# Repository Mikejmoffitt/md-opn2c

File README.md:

# MD用YM3438アダプター・MD YM3438 Adapter

# 概要・Overview
このアダプターでメガドライブ初代はYM3438(OPN2C)が対応できるようになります。　元々の音源のステータスレジスターの読み込みの違いを解決するとジックがついています。　その上[オープンソースのトリップルバイパス](https://github.com/tianfeng33/triple-bypass-Version-2))より綺麗な音源のミクサーとバッファーがついていて、元々のヘッドホンも専用ライン出力が使えるようになります。

元々のFM音源(YM2612)を抜いて使用することも可能です。　その場合は[3BP](https://github.com/tianfeng33/triple-bypass-Version-2)と同じような使い方になります。　その場合でもヘッドホンもラインアウトも利用できます。

メガドラVA0の基板を参考しながら書いたんですが、基本的にすべての初代の基板は互換はずです。

This adapter facilitates the install of a YM3438 (OPN2C) in a Sega Mega Drive or Genesis console. Glue logic is present to solve status read bugs that invoke different behavior between the original YM2612 and the CMOS YM3438. In addition, a mixing and buffering circuit (courtesy of [the open source Triple Bypass PCB](https://github.com/tianfeng33/triple-bypass-Version-2)) to both handle the new YM3438 and also provide clean mixing for other signals. The buffer circuit also has provisions to output audio to the original signal path, so that the mono audio output and the headphone jack both work as designed.

An original YM2612 may also be installed, in which case this PCB simply provides a new mixing circuit and buffer, similar to the [Triple Bypass PCB](https://github.com/tianfeng33/triple-bypass-Version-2)).

These instructions were written using a Japanese VA0 unit as a reference, but principally can apply to any Megadrive or Genesis with a YM2612 in it.

## 互換の本体・Compatibility

メガドライブ（初代）VA0-VA6は互換です。 ジェネシス２のVA3でも動くかもしれませんが、未確認なので一応保証ができません。
Compatible with Genesis 1 / Megadrive 1 VA0-VA6. Genesis 2 VA3 (with discrete YM2612) may work, but has not been tested, and I cannot provide installation instructions at this time.

# 設置・Installation

## マザーの修正・Motherboard Preparation

マザーに付ける前に修正が必要です．

With the adapter unit ready, some work must be done to the Megadrive motherboard.

YM2612を外して、どこか保存しします。（依頼要らないけど捨てないでください！）　下の縦列のコンデンサーも外しましょう。(C40, C41, C42, C43, C44, C61, C62)

Desolder and remove the YM2612, and the column of capacitors below it (C40, C41, C42, C43, C44, C61, and C62).

底面に赤く示している部品を外します。 (R34, R37, R40, R41, C45, C46, C47, C48)。　右の黄色いやつを外して、左のバツが付いている黄色い部品をその位置に移動します (R53/R43, R40/R41)。　C41とC43の穴にリンクを入れてください。

下面に印刷がないので下の絵を参考してください。

On the underside, remove the components marked in red (R34, R37, R40, R41, C45, C46, C47, C48). Remove the components marked in yellow (R53 and R43) and move them to the spot marked in yellow (R40 and R41). Install a link between the two pins of capacitors C41 and C43.

As there is no silkscreen on the underside of most revisions, the diagram will be a helpful reference. 

新しいミックスされた音声は元々のFM音源の端子に入ります（21ピンと20ピン）。　そのために元々のヘッドホンもモノの出力が使えます。

The new audio will enter through what used to be the MOL and MOR pins for the OPN2, at pins 21 and 20 respectively. The mixed stereo signals enter the original mixing circuit alone, where it then enters the headphone amp as well as the mono mixdown for the CXA-1145.

## 音源付け方・Installation of FM Sound Source

YM3438か先抜いたYM2612をアダプターの上面に付けます。　下面にピンが邪魔になってしまうので上面にハンダ付けても大丈夫です。　音源のICは完全に平にならないんですが、全ての端子がちゃんとついていたら問題がありません　(少距離は大丈夫です)。

アダプターのウラ面にジャンパーがあります。　音源の種類によって左側か右側を半田で閉めて下さい。　両方のジャンパーを同じ設置するようにご注意下さい。

Attach either a YM3438 or the previously removed YM2612 in the open position on the adapter PCB. As the header pins on the underside may obstruct your soldering, it is fine to apply solder on the top side. The IC may not lay perfectly flat, but if all pins are firmly soldered a slight distance is acceptable.

On the underside of the adapter, use solder to close the jumpers based on the sound source type. You must set both sets of jumpers in the same configuration.

| 設定Config | IC類Chip |
|------------|----------|
| `(---  )`  | YM2612   |
| `(  ---)`  | YM3438   |

YM2612の場合は、音源の20/21ピンからグラウンド(19ピン）に2.2k抵抗器を付けて下さい。　次の改正に修正しますが、とりあえずこの小さい改造が必要になります。

In the case of a YM2612, attach two 2.2k resistors between pins 20/21 and ground (pin 19), as the YM2612 requires pulldown resistors. Pads for this will be incorporated in a future revision.

## 基板の付け方・Installation in Megadrive

先の準備を完全似できたか確認しておいてください。

Please be sure you have completed the Motherboard Preparation steps first.

YM2612の位置にYM3438のアダプターを入れて、下面にハンダ付けます。　上面に5本の配線が必要です。　下の表を参考して

Place the assembled YM3438 adapter unit in the position that once held the original YM2612, and solder it in place on the underside. On the top, five wires are necessary to feed in the various audio signals that compliment the FM sound source. The table below describes the positions shown in the annotated picture below.

| 信号Signal | 出所Location |
|------------|--------------|
| SL1        | C42 (-)      |
| SL2        | C61 (-)      |
| SR1        | C44 (-)      |
| PSG        | C40 (-)      |
| SR2        | C62 (-)      |

これで、どうやって出力を本体外に出すか自分の決まりです。　もしヘッドホンの端子が十分でしたらここまでストップしても大丈夫です。　しかし、ヘッドホンのアンプより直接LINE出力したらノイズが少なくなるので、LINEの出力はおすすめです。

アダプターにOUTのパッドがあります。　そこに配線付けて端子に繋げたらLINEの出力が可能です。

With everything installed, it's up to you how you want to route the audio out. If the headphone jack alone is adequate, you may stop here. However, I recommend a dedicated line out connection, as the headphone amp does introduce some noise.

The 'LINE OUT' pads are present so you may run a stereo output to the back of the console, or to some other connector of your choosing. Stereo audio will be present via the headphone jack, and mono audio will be delivered out of the rear A/V connector.

# フィルター調整・Filter Adjustment

アダプタのLPFフィルターの遮断周波数は約16KHzになっていますが、もしVA3みたいな~3KHzは希望だったらコンデンサー交換通じて可能です。　示しているコンデンサーを150Pfに交換すると、LPFの遮断周波数は~3KHzになります。　元々のは33pFです。

The filter situated on the adapter has a fairly high cutoff frequency of about 16KHz. Unlike the triple bypass PCB, there isn't a selection of filter parameters, but if a stronger filter that sounds similar to the VA3 is desired, you may exchange the two highlighted capacitors for 150pF units to achieve a ~3.5KHz cutoff. The originals are 33pF.

# バージョン・Version History

## 1.0.0

テスト用基板です。　YM2612対応パッドがなくてYM3438だけを確認しました。

This version was made for testing. Pads to cooperate with YM2612 were not considered, and the operation of YM3438 was confirmed with this.

## 1.0.1

初版です。

First release.

## 1.0.2

形関わらずYM2612用レジスターを追加シました。

Optional pull-down resistors for YM2612 compatibility were added.

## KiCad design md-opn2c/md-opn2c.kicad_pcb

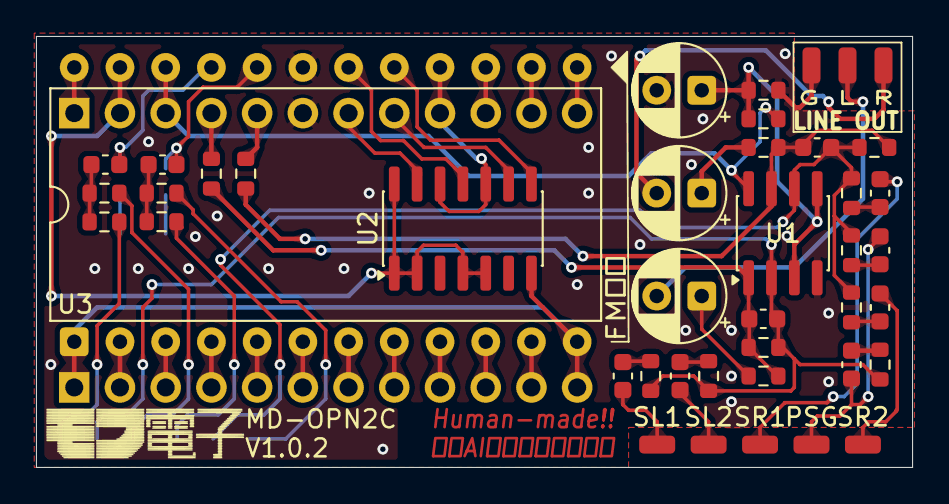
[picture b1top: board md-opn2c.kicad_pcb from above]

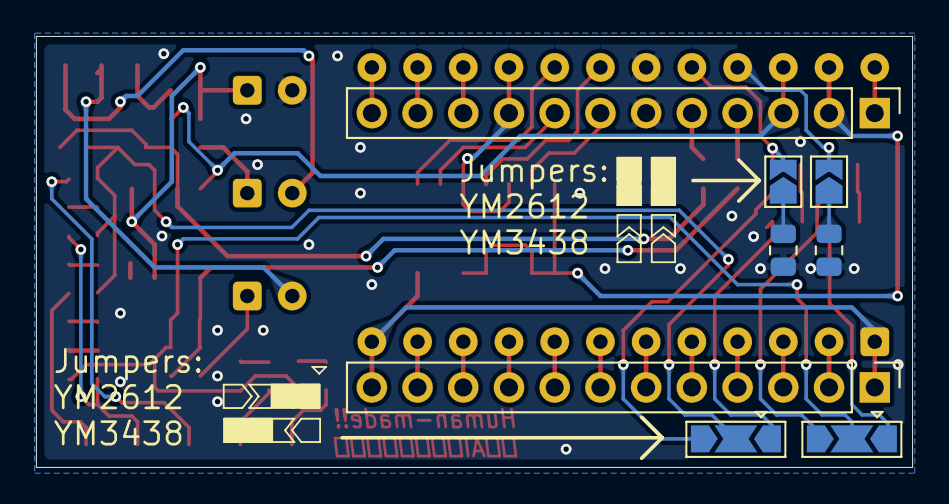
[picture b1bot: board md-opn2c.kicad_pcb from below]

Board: 2 copper layers, 48.7 x 23.9 mm, 50 parts (8 on the bottom side), 55 nets.

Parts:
C1, C2: 10uF/16V; C_0603_1608Metric
C3, C4, C5, C6, C7, C8: 1uF/16V; C_0603_1608Metric
C9, C10: 33pF/50V; C_0603_1608Metric
C11: 10uF/16V; CP_Radial_D5.0mm_P2.50mm
C12, C13: 47uF/50V; CP_Radial_D5.0mm_P2.50mm
IN_PSG1: TestPoint_Small; SolderWirePad_1x01_SMD_1x2mm
IN_SL1, IN_SL2: TestPoint_Small; SolderWirePad_1x01_SMD_1x2mm
IN_SR1, IN_SR2: TestPoint_Small; SolderWirePad_1x01_SMD_1x2mm
J1, J2: Conn_01x12_Pin; PinHeader_1x12_P2.54mm_Vertical
JP1, JP2: SolderJumper_3_Open; SolderJumper-3_P2.0mm_Open_TrianglePad1.0x1.5mm
JP3, JP4: SolderJumper_2_Open; SolderJumper-2_P1.3mm_Open_TrianglePad1.0x1.5mm
OUT_GND1: TestPoint_Small; SolderWirePad_1x01_SMD_1x2mm
OUT_L1: TestPoint_Small; SolderWirePad_1x01_SMD_1x2mm
OUT_R1: TestPoint_Small; SolderWirePad_1x01_SMD_1x2mm
R2, R3: 2.2k; R_0805_2012Metric
R8, R9, R22, R23: 100k; R_0603_1608Metric
R10, R11, R12, R13, R14, R15: 210k; R_0603_1608Metric
R16, R17: 300k; R_0603_1608Metric
R18, R19: 330; R_0603_1608Metric
R20, R21, R24, R25: 10k; R_0603_1608Metric
U1: TL972; SOIC-8_3.9x4.9mm_P1.27mm
U2: 74HCT08; SOIC-14_3.9x8.7mm_P1.27mm
U3: YM3438; DIP-24_W15.24mm

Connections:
/BIAS_2_5V: C11.1, R20.1, R21.2, U1.3 (+), U1.5 (+)
/BUF_L: C9.2, R16.2, R18.1, R22.1, U1.1
/BUF_R: C10.2, R17.2, R19.1, R23.1, U1.7
/MIX_L: C9.1, JP1.2 (C), R10.2, R12.2, R14.2, R16.1, U1.2 (-)
/MIX_R: C10.1, JP2.2 (C), R11.2, R13.2, R15.2, R17.1, U1.6 (-)
/OPN2C_MOL: C1.1, JP3.2 (B), U3.21 (MOL)
/OPN2C_MOR: C2.1, JP4.2 (B), U3.20 (MOR)
/OPN_A0: J2.8, U2.9
/OPN_A0_FILTERED: U2.8, U3.17 (A_{0})
/OPN_A1: J2.7, U2.13
/OPN_A1_FILTERED: U2.11, U3.18 (A_{1})
/OPN_D0: J1.2, U3.2 (D_{0})
/OPN_D1: J1.3, U3.3 (D_{1})
/OPN_D2: J1.4, U3.4 (D_{2})
/OPN_D3: J1.5, U3.5 (D_{3})
/OPN_D4: J1.6, U3.6 (D_{4})
/OPN_D5: J1.7, U3.7 (D_{5})
/OPN_D6: J1.8, U3.8 (D_{6})
/OPN_D7: J1.9, U3.9 (D_{7})
/ORIG_OUT_L: J2.4, R22.2
/ORIG_OUT_R: J2.5, R23.2
/OUT_L: C12.2, OUT_L1.1 (1_1)
/OUT_R: C13.2, OUT_R1.1 (1_1)
/PSG: C7.1, C8.1, IN_PSG1.1 (1_1)
/SL1: C3.1, IN_SL1.1 (1_1)
/SL2: C5.1, IN_SL2.1 (1_1)
/SR1: C4.1, IN_SR1.1 (1_1)
/SR2: C6.1, IN_SR2.1 (1_1)
/~OPN_CLK: J2.1, U3.24 (ΦM)
/~OPN_CS: J2.11, U3.14 (~CS)
/~OPN_IC: J1.11, U3.11 (~IC)
/~OPN_IRQ: J2.12, U3.13 (~IRQ)
/~OPN_RD: J2.9, U2.10, U2.12, U3.16 (~RD)
/~OPN_TEST: J1.10, U3.10 (~TEST)
/~OPN_WR: J2.10, U3.15 (~WR)
GND: J1.1, J1.12, U2.7 (GND), U3.1 (GND), U3.12 (GND)
GNDA: C11.2, J2.6, OUT_GND1.1 (1_1), R2.2, R3.2, R21.1, U1.4 (V-), U3.19 (AGND)
unnamed: C1.2, R8.1, R24.2
unnamed: C2.2, R9.1, R25.2
unnamed: C3.2, R10.1
unnamed: C4.2, R11.1
unnamed: C5.2, R12.1
unnamed: C6.2, R13.1
unnamed: C7.2, R14.1
unnamed: C8.2, R15.1
unnamed: C12.1, R18.2
unnamed: C13.1, R19.2
unnamed: JP1.1 (A), R24.1
unnamed: JP1.3 (B), R8.2
unnamed: JP2.1 (A), R25.1
unnamed: JP2.3 (B), R9.2
unnamed: JP3.1 (A), R2.1
unnamed: JP4.1 (A), R3.1
VCC: J2.2, U2.1, U2.2, U2.4, U2.5, U2.14 (VCC), U3.23 (V_{CC})
VCCA: J2.3, R20.2, U1.8 (V+), U3.22 (AV_{CC})

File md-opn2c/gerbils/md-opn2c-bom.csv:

"Reference","Qty","Value","Footprint","Datasheet","PN","Digikey PN"
"C1,C2","2","10uF/16V","Capacitor_SMD:C_0603_1608Metric","https://mm.digikey.com/Volume0/opasdata/d220001/medias/docus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","GRM188R61C106MAALD","490-10729-2-ND"
"C3,C4,C5,C6,C7,C8","6","1uF/16V","Capacitor_SMD:C_0603_1608Metric","https://mm.digikey.com/Volume0/opasdata/d220001/medias/docus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","EMK107B7105KA-T","587-1241-2-ND"
"C9,C10","2","33pF/50V","Capacitor_SMD:C_0603_1608Metric","https://yageogroup.com/content/datasheet/asset/file/KEM_C100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","C0603C330K4HACTU","399-C0603C330K4HACTUTR-ND"
"C11","1","10uF/16V","Capacitor_THT:CP_Radial_D5.0mm_P2.50mm","https://www.we-online.com/components/products/datasheet/8600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","860010372001","732-8593-1-ND"
"C12,C13","2","47uF/50V","Capacitor_THT:CP_Radial_D5.0mm_P2.50mm","https://www.we-online.com/components/products/datasheet/8600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","860020472006","732-8823-1-ND"
"J1,J2","2","Conn_01x12_Pin","Connector_PinHeader_2.54mm:PinHeader_1x12_P2.54mm_Vertical","https://app.adam-tech.com/products/download/data_sheet/20160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","PH1-12-UA","2057-PH1-12-UA-ND"
"R8,R9,R22,R23","4","100k","Resistor_SMD:R_0603_1608Metric","https://www.koaspeer.com/pdfs/RK73H.pdf","RK73H1JTTD1003F","2019-RK73H1JTTD1003FTR-ND"
"R10,R11,R12,R13,R14,R15","6","210k","Resistor_SMD:R_0603_1608Metric","https://www.koaspeer.com/pdfs/RK73H.pdf","RK73H1JTTD2103F","2019-RK73H1JTTD2103FTR-ND"
"R16,R17","2","300k","Resistor_SMD:R_0603_1608Metric","https://www.vishay.com/docs/28700/mcx0x0xpre.pdf,https://www.vishay.com/docs/28700/mcx0x0xpre.pdfhttps://www.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","MCT06030D3003BP500","749-MCT06030D3003BP500TR-ND"
"R18,R19","2","330","Resistor_SMD:R_0603_1608Metric","https://www.koaspeer.com/pdfs/SG73P.pdf","SG73P1JTTD3300F","2019-SG73P1JTTD3300FTR-ND"
"R20,R21,R24,R25","4","10k","Resistor_SMD:R_0603_1608Metric","https://industrial.panasonic.com/cdbs/www-data/pdf/RDA0000/A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","ERJ-3EKF2103V","P210KHTR-ND"
"U1","1","TL972","Package_SO:SOIC-8_3.9x4.9mm_P1.27mm","https://www.ti.com/general/docs/suppproductinfo.tsp?distId=1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","TL972IDR","296-22842-2-ND"
"U2","1","74HCT08","Package_SO:SOIC-14_3.9x8.7mm_P1.27mm","https://www.ti.com/lit/ds/scls063e/scls063e.pdf","SN74HCT08DR","296-14862-2-ND"
